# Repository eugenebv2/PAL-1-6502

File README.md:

# PAL-1-6502
A KIM-1 Replica.

PAL-1 with Motherboard Expansion Kit, 32KB RAM Expansion Kit, 2nd RIOT Expansion Kit, ROM Expansion Kit V1.2

PI1541 from: https://github.com/tebl/C64-Pi1541-III

And the Expansion ROM image from: https://groups.google.com/g/pal6502/c/loMjudhtTIg

Let the PAL-1 running xKIM and BASIC with PI1541 Disk Dir. LOAD, SAVE function.

<hr>

![alt text][def1]

[def1]: Photos/IMG_4461.jpg

![alt text][def2]

[def2]: Photos/CIMG0452.JPG

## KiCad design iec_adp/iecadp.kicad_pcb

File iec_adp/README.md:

First time using the KiCAD.

the Adapter was not test yet.

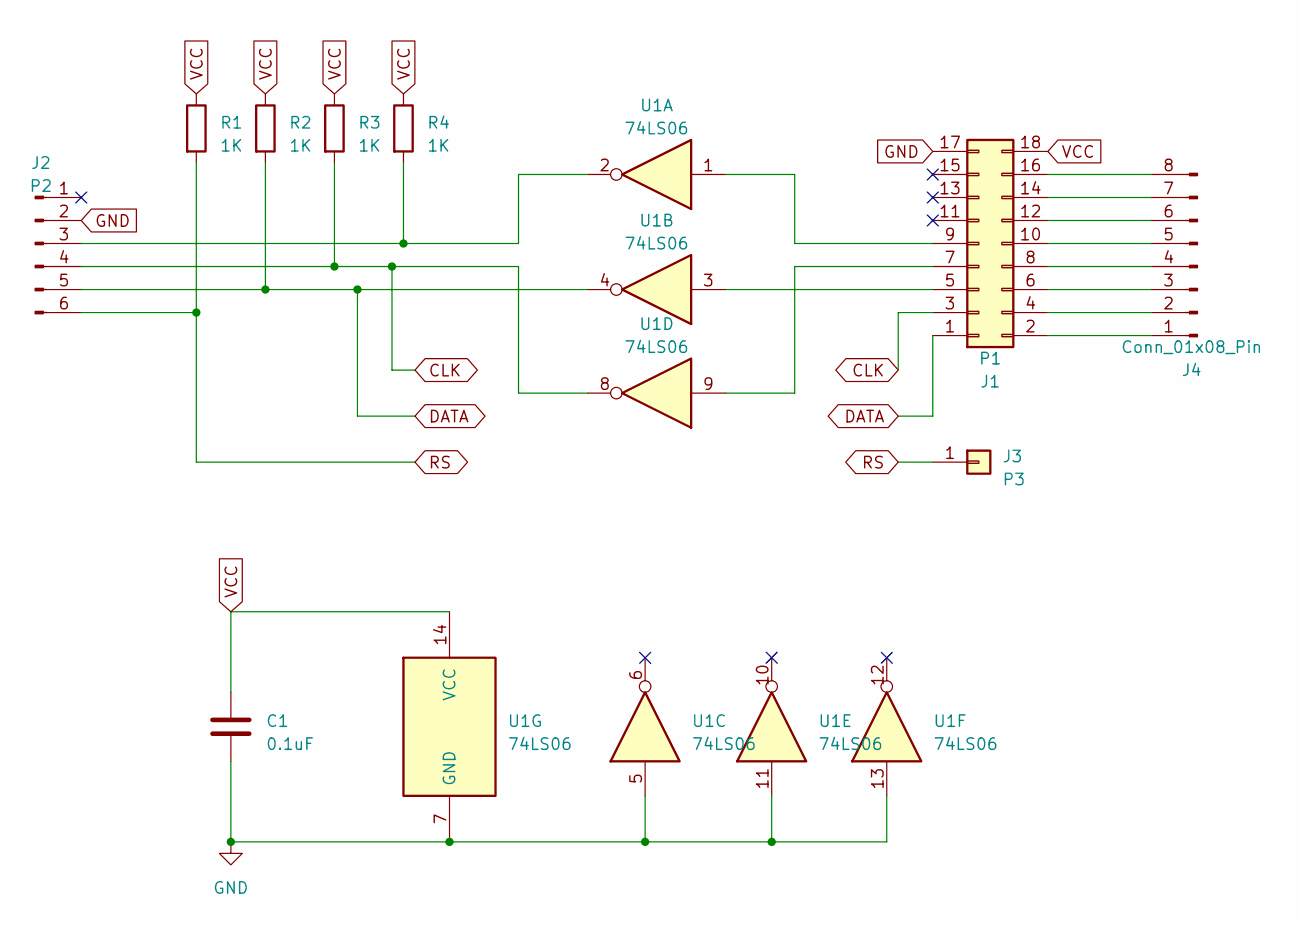
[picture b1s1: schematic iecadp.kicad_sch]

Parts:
C1: 0.1uF; C_Disc_D5.1mm_W3.2mm_P5.00mm
J1: P1; PinHeader_2x09_P2.54mm_Vertical
J2: P2; PinHeader_1x06_P2.54mm_Vertical
J3: P3; PinHeader_1x01_P2.54mm_Vertical
J4: Conn_01x08_Pin; PinHeader_1x08_P2.54mm_Vertical
R1, R2, R3, R4: 1K; R_Axial_DIN0207_L6.3mm_D2.5mm_P10.16mm_Horizontal
U1: 74LS06; DIP-14_W7.62mm_Socket

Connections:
CLK: J1.3, J2.4, R3.2, U1.8
DATA: J1.1, J2.5, R2.2, U1.4
GND: C1.2, J1.17, J2.2, U1.5, U1.7 (GND), U1.11, U1.13
unnamed: J1.2, J4.1
unnamed: J1.4, J4.2
unnamed: J1.5, U1.3
unnamed: J1.6, J4.3
unnamed: J1.7, U1.9
unnamed: J1.8, J4.4
unnamed: J1.9, U1.1
unnamed: J1.10, J4.5
unnamed: J1.12, J4.6
unnamed: J1.14, J4.7
unnamed: J1.16, J4.8
unnamed: J2.3, R4.2, U1.2
RS: J2.6, J3.1, R1.2
VCC: C1.1, J1.18, R1.1, R2.1, R3.1, R4.1, U1.14 (VCC)

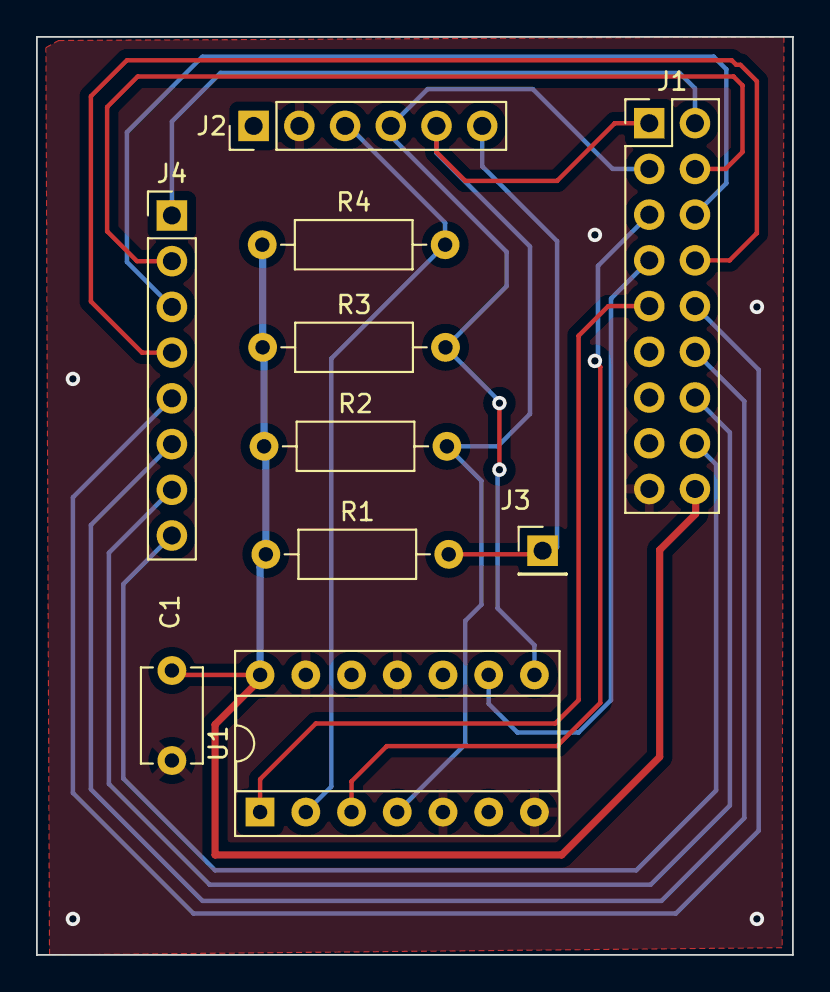
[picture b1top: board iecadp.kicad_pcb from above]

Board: 2 copper layers, 42.0 x 51.0 mm, 10 parts (0 on the bottom side), 17 nets.
